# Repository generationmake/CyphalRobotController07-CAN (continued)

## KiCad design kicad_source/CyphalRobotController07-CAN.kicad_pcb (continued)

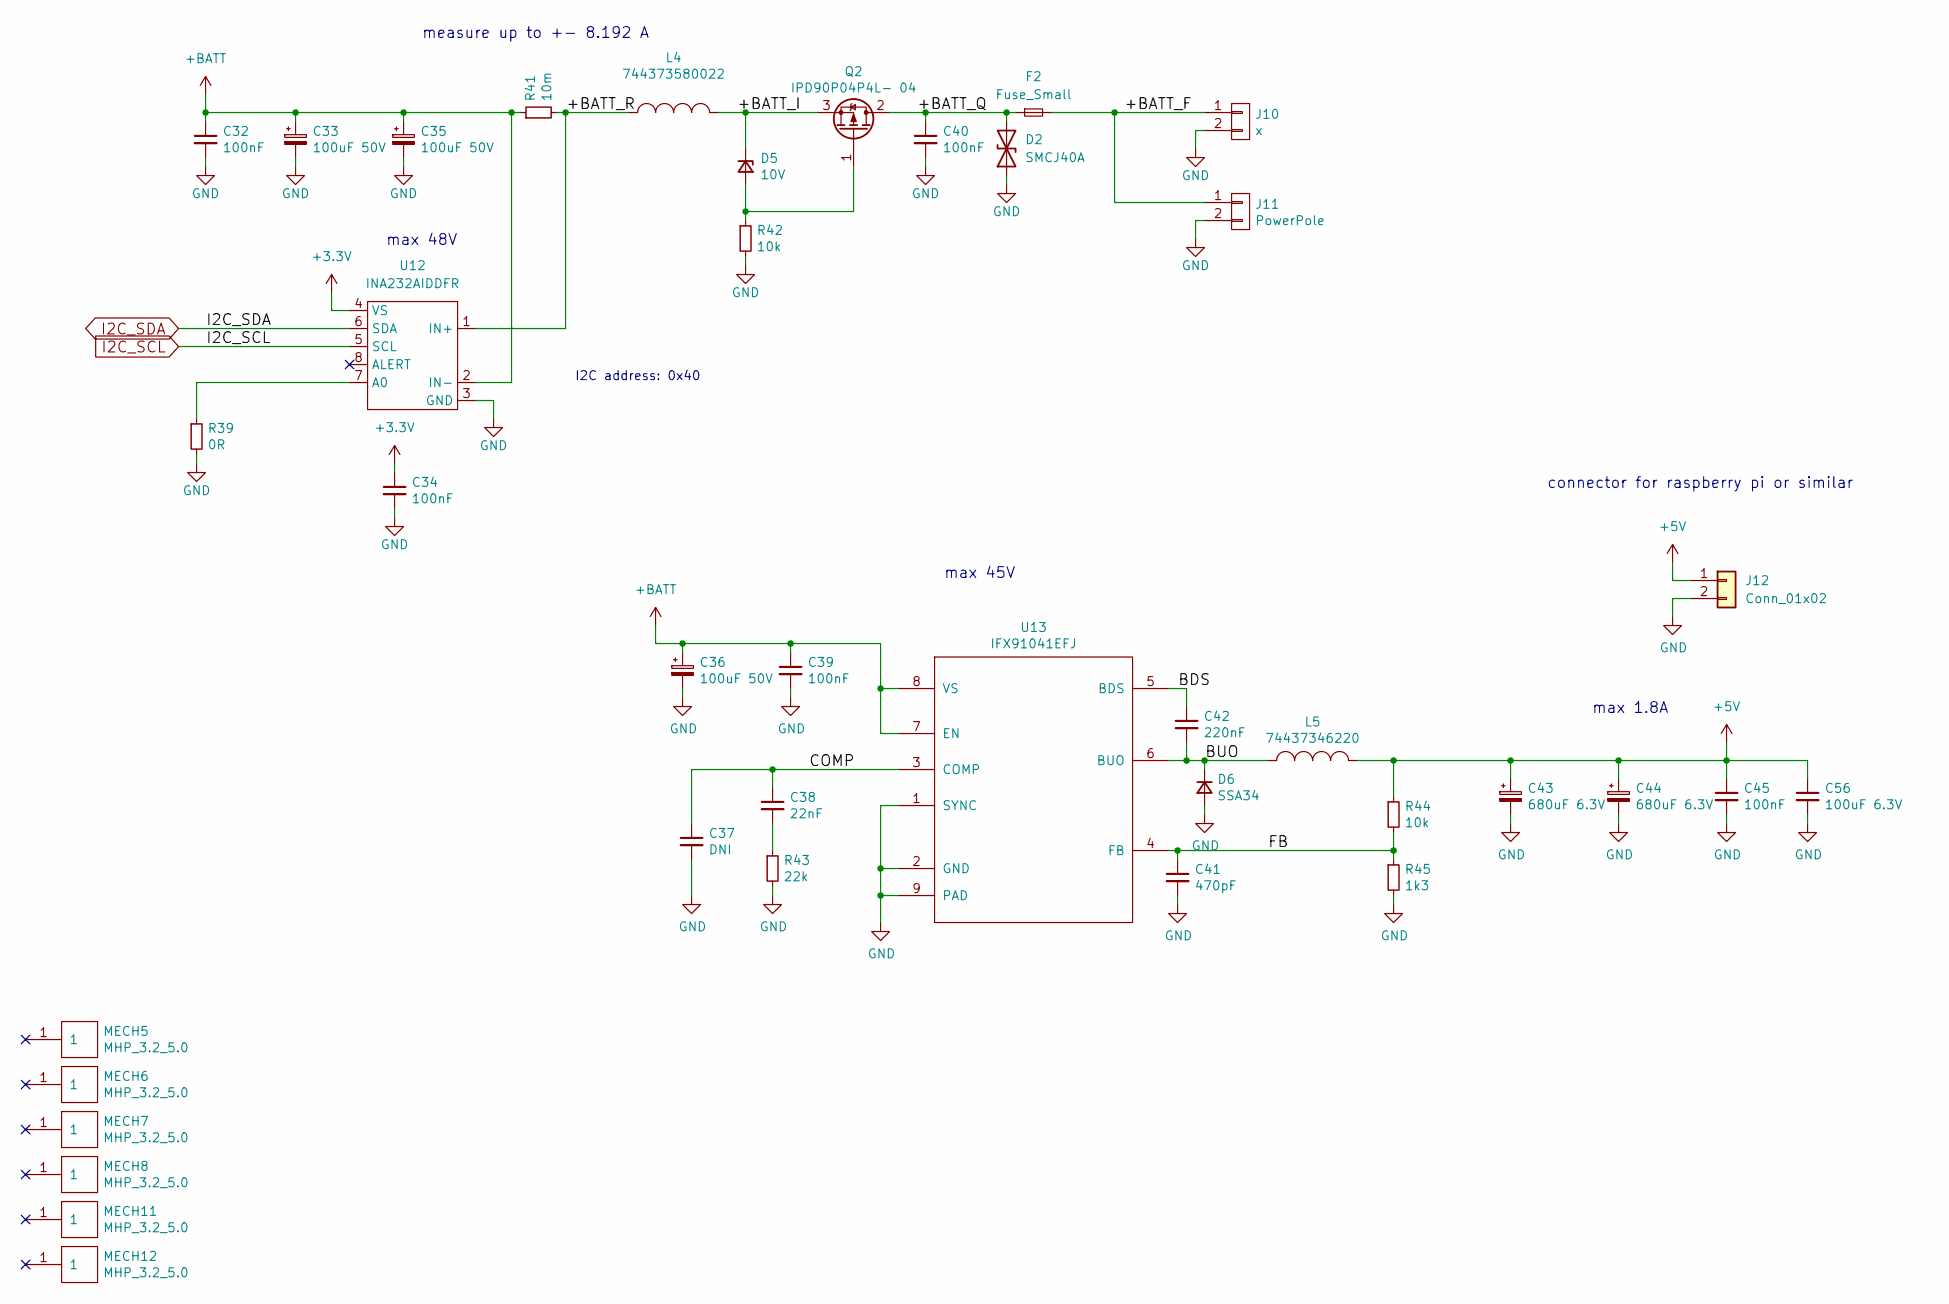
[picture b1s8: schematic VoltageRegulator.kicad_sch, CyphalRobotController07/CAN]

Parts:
C32, C34, C39, C40, C45: 100nF; C_0603_1608Metric
C33, C35, C36: 100uF 50V; CP_Elec_6.3x7.7
C37: DNI; C_0603_1608Metric
C38: 22nF; C_0603_1608Metric
C41: 470pF; C_0603_1608Metric
C42: 220nF; C_0603_1608Metric
C43, C44: 680uF 6.3V; CP_Elec_6.3x7.7
C56: 100uF 6.3V; C_1210_3225Metric
D2: SMCJ40A; D_SMC
D5: 10V; D_SOD-123
D6: SSA34; D_SMA
F2: Fuse_Small; Fuseholder_Blade_ATO_Littelfuse_Pudenz_2_Pin
J10: x; PhoenixContact_MCV_1,5_2-G-3.81_1x02_P3.81mm_Vertical
J11: PowerPole; POWERPOLE_2
J12: Conn_01x02; PhoenixContact_MCV_1,5_2-G-3.81_1x02_P3.81mm_Vertical
L4: 744373580022; L_Wuerth_HCM-1052
L5: 74437346220; L_Wuerth_HCI-7050
MECH5, MECH6, MECH7, MECH8, MECH11, MECH12: MHP_3.2_5.0; MHP_3.2_5.8
Q2: IPD90P04P4L- 04; TO-252-2
R39: 0R; R_0603_1608Metric
R41: 10m; R_1206_3216Metric
R42, R44: 10k; R_0603_1608Metric
R43: 22k; R_0603_1608Metric
R45: 1k3; R_0603_1608Metric
U12: INA232AIDDFR; SOT-23-8
U13: IFX91041EFJ; SOIC-8-1EP_3.9x4.9mm_P1.27mm_EP2.29x3mm

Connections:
+3.3V: C34.1, U12.4 (VS); also elsewhere on the board
+5V: C43.1, C44.1, C45.1, C56.1, J12.1, L5.2, R44.1; also elsewhere on the board
+BATT: C32.1, C33.1, C35.1, C36.1, C39.1, R41.1, U12.2 (IN-), U13.7 (EN), U13.8 (VS); also elsewhere on the board
/VoltageRegulator/+BATT_F: F2.2, J10.1, J11.1
/VoltageRegulator/+BATT_I: D5.1 (K), L4.2, Q2.3 (S)
/VoltageRegulator/+BATT_Q: C40.1, D2.2 (A2), F2.1, Q2.2 (D)
/VoltageRegulator/+BATT_R: L4.1, R41.2, U12.1 (IN+)
/VoltageRegulator/BDS: C42.1, U13.5 (BDS)
/VoltageRegulator/BUO: C42.2, D6.1 (K), L5.1, U13.6 (BUO)
/VoltageRegulator/COMP: C37.1, C38.1, U13.3 (COMP)
/VoltageRegulator/FB: C41.1, R44.2, R45.1, U13.4 (FB)
GND: C32.2, C33.2, C34.2, C35.2, C36.2, C37.2, C39.2, C40.2, C41.2, C43.2, C44.2, C45.2, C56.2, D2.1 (A1), D6.2 (A), J10.2, J11.2, J12.2, R39.2, R42.2, R43.2, R45.2, U12.3 (GND), U13.1 (SYNC), U13.2 (GND), U13.9 (PAD); also elsewhere on the board
I2C_SCL: U12.5 (SCL); also elsewhere on the board
I2C_SDA: U12.6 (SDA); also elsewhere on the board
unnamed: C38.2, R43.1
unnamed: D5.2 (A), Q2.1 (G), R42.1
unnamed: R39.1, U12.7 (A0)

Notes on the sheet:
connector for raspberry pi or similar
I2C address: 0x40
max 1.8A
measure up to +- 8.192 A
max 48V
max 45V

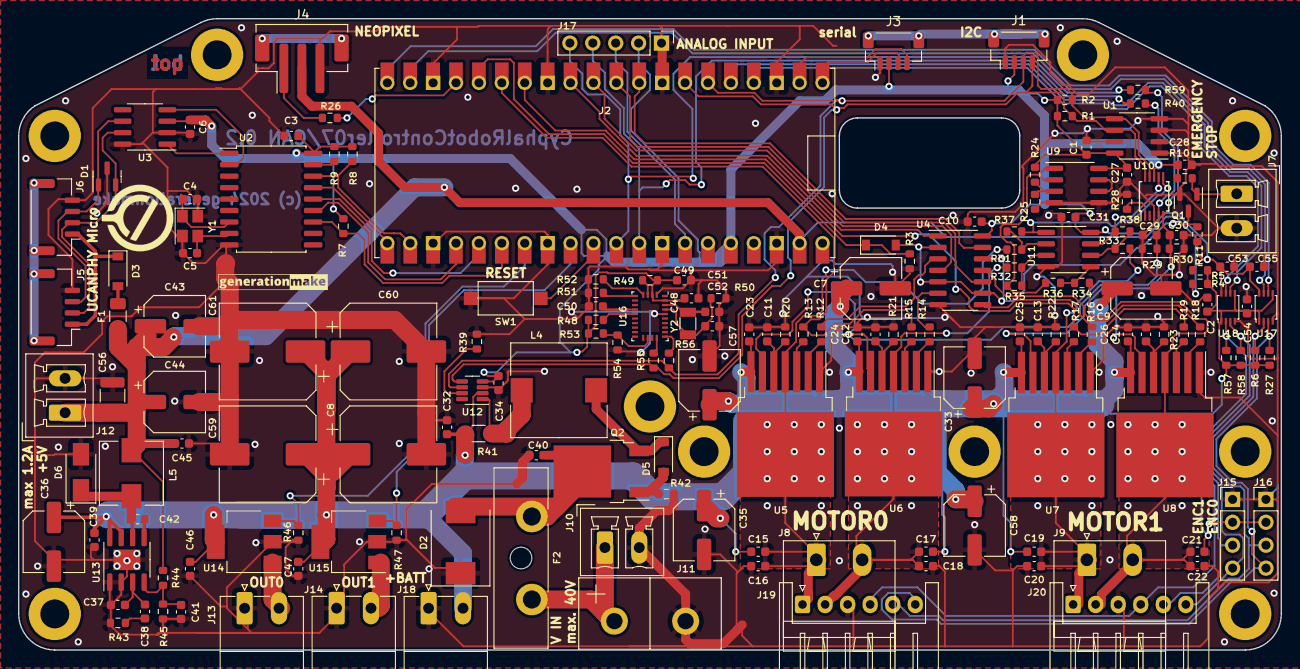
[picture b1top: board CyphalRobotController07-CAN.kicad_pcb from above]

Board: 2 copper layers, 140.0 x 70.0 mm, 186 parts (0 on the bottom side), 105 nets.

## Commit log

2023-07-24 generated kicad project
2023-07-24 added first schematic pdf
2023-07-24 updated layout
2023-08-07 moved input circuit to voltage regulator side
2023-08-07 added INA226
2023-08-07 added BNO085
2023-09-30 added page with outputs
2023-09-30 added power pole and fuse
2023-10-01 started layout
2023-10-01 made first draft of placement
2023-10-01 made first draft of layout
2023-10-01 updated schematic pdf
2023-10-01 added step file
2023-10-01 reworked shape of PCB to fit into T07, added hole for USB connector
2023-10-02 added connector for quad encoder
2023-10-02 finished layout
2023-10-02 added images
2023-10-02 updated step file
2023-10-02 renamed files
2023-10-02 reworked readme
2023-11-15 updated 3d model to fit to reality
2023-12-03 added license
2023-12-03 combined 3.3V nets
2023-12-03 changed R45 to 1k3
2023-12-03 added weak pull down on EM_STOP_D
2023-12-03 added always on connector for +BATT
2023-12-03 added JST XH connector for motor and encoder
2024-01-04 moved motor controller further up to have more space for connectors
2024-01-04 changed motor connector, connected encoder
2024-01-07 added pinouts to readme
2024-01-08 beautified layout near encoders
2024-01-15 added some labels
2024-01-15 added level converters on encoder inputs
2024-01-21 finished layout near encoder level converter
2024-01-21 used raspberry pi pico with headers
2024-01-21 added protection on CAN
2024-01-21 added tvs diode on input
2024-01-21 replaced tantal with electrolytic capacitors
2024-01-22 checked supply voltage of parts
2024-01-22 replaced INA226 by INA232 to support up to 40V
2024-01-22 connected current sense output to analog in of RP2040
2024-01-22 fixed some drc errors
2024-01-24 fixed some drc errors, made designators smaller
2024-01-24 beautified layout
2024-01-25 updated 3d models
2024-01-25 updated schematic history, updated schematic pdf
2024-01-25 updated images
2024-02-13 added dimension pdf
